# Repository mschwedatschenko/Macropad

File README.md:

# 3x3 Macropad Custom PCB 
This PCB was designed in KiCad and programmed in Arduino IDE using C++. I used OSHPark as my manufacturer of choice, and got some beautiful purple PCBs with ENIG surface finish. The Macropad acts as a HID, with each key representing a number 1-9. These keys can be programmed to be anything the user wants.

## Pictures

Here's the schematic of my design:

Here's the PCB layout of my design:

## Notes
I made the switch footprints far too close to one another, so I had to sand down the switches in order for them to be soldered correctly. This design does not support keycaps. Additionally, future iterations should include the Arduino Micro on the board itself, as it is a pain to have the Arduino Micro hanging off.

I'm currently in the process of making a 60% Keyboard PCB. 

## Purpose
After losing access to my mechanical keyboard I used for a while and just relying on my laptop's built-in keyboard, I had the desire to make my own mechanical keyboard completely from scratch. This macropad serves as a precursor to a 60% keyboard I hope to create during this academic year using a bare ATMega32U4 Microcontroller rather than an Arduino Micro, and to test the waters with the project on a smaller scale. 

It made sense to stick with the Arduino Micro for the microcontroller for this project since I will be strictly using through-hole soldering. With the 60% project, having regular access to WPI's reflow oven will yield hopefully better results using SMT soldering (hand soldering all of the pins on the microcontroller sounds like a nightmare).

I hope to make the switches on the 60% keyboard hot-swappable. I used Cherry MX switches for this macropad and soldered them directly to the PCB.

## BOM
Arduino Micro (alternative knockoff linked here)
https://www.amazon.com/dp/B0B6HYLC44?ref=ppx_yo2ov_dt_b_fed_asin_title 

9x THT Diodes
https://www.digikey.com/en/products/detail/onsemi/1N4148/458603 

9x Cherry MX Switches
https://www.digikey.com/en/products/detail/cherry-americas-llc/MX1A-E1NW/20180

1x 2x12 Pin Header
https://www.mouser.com/ProductDetail/Amphenol-FCI/67996-126HLF?qs=zh4O8xspOuwM2BHmqRMfPg%3D%3D&countryCode=US&currencyCode=USD 

Female to Female Jumper Wires
https://www.amazon.com/California-JOS-Breadboard-Optional-Multicolored/dp/B0BRTKTV64?crid=1LACSR79FHSYC&dib=eyJ2IjoiMSJ9.ibSfPMW-D8UnuoyT0yyf3D_lk7qt6Xtf-hseYz3CHE_PSs4KAuAkM15Fy0qTHeL-0sbmZ6xvudwt1mH7ECdw52J8qVeg-_UcOEXbhjt0zu6y_XCODlAWuh6MgwS7A1VJKjYsNmwjxwCTXuMRC-D0OfljqHtJ6zQDzKQ3gSM8hIwX8KOZwJewJkuHyeDDnSRg3klQF3WwJ22bo-lTGaa8bweF99vKP4XyfbRqS5AhPqo.L_8eHglXmOdtWOBj3pQvrHvJbkccanVmh4Z13YR6j0w&dib_tag=se&keywords=jumper%2Bwires%2Bfemale%2Bto%2Bfemale&qid=1765915770&sprefix=jumper%2Bwires%2Bfemale%2Bto%2Bfemale%2Caps%2C134&sr=8-5&th=1

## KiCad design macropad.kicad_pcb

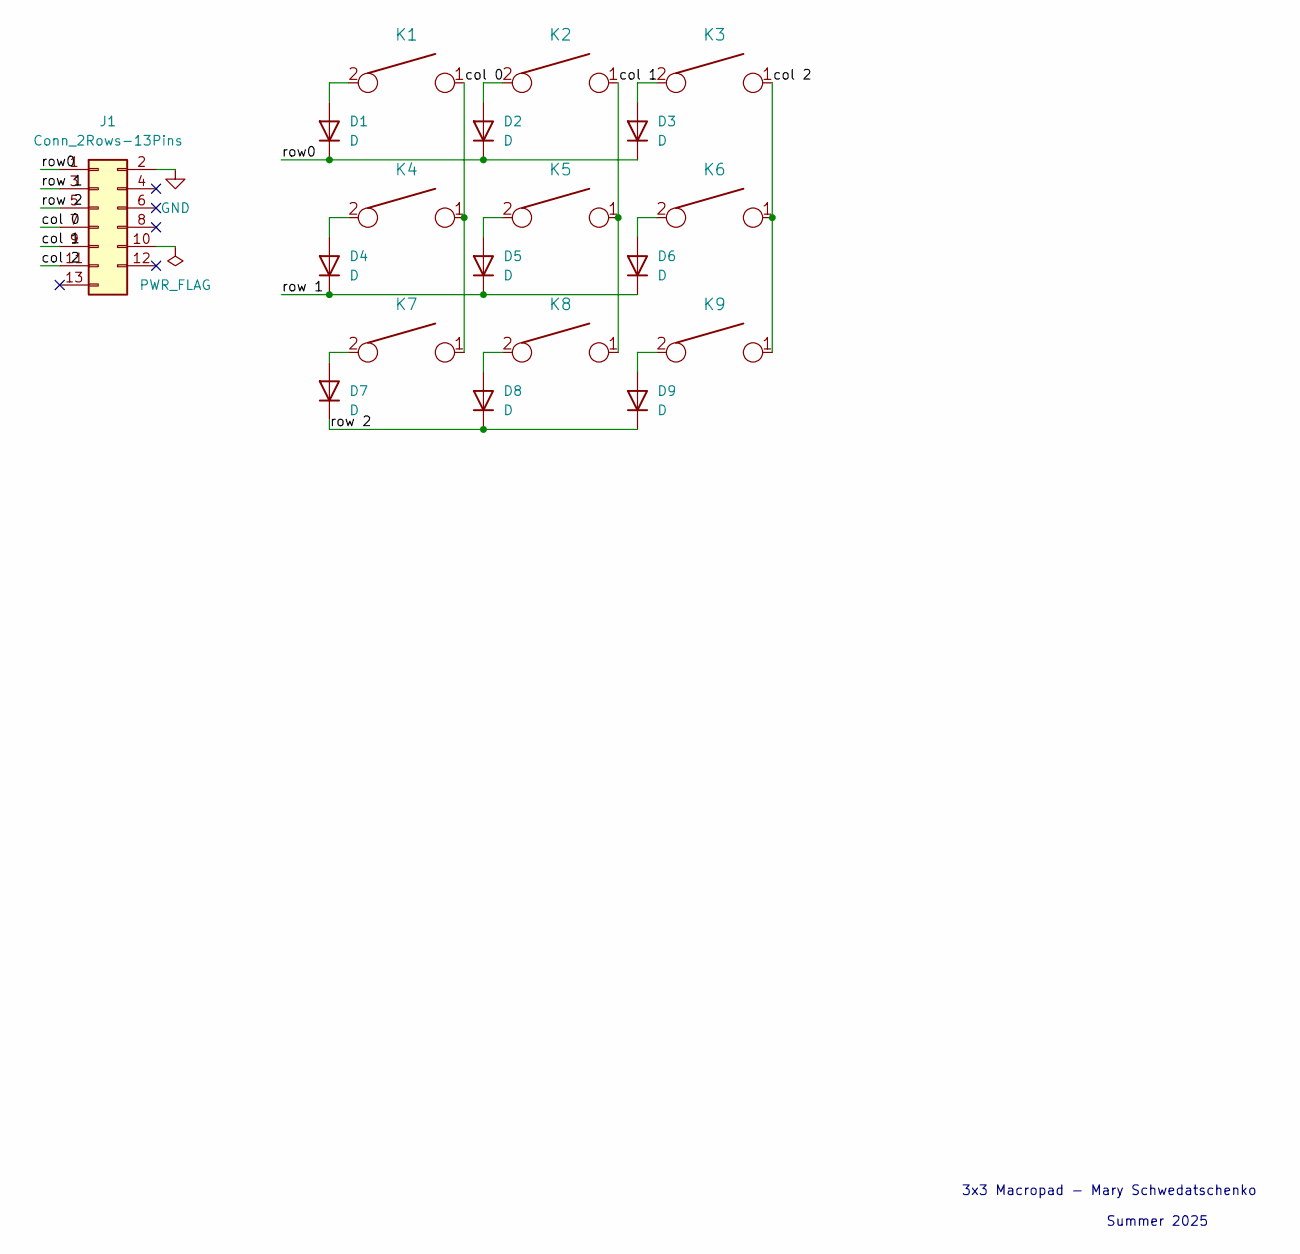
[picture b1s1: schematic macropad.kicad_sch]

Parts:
D1, D2, D3, D4, D5, D6, D7, D8, D9: D; D_DO-35_SOD27_P5.08mm_Vertical_AnodeUp
J1: Conn_2Rows-13Pins; PinHeader_2x13_P2.54mm_Vertical
K1, K2, K3, K4, K5, K6, K7, K8, K9: KEYSW; SW_Cherry_MX_1.00u_PCB

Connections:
/col 0: J1.7, K1.1, K4.1, K7.1
/col 1: J1.9, K2.1, K5.1, K8.1
/col 2: J1.11, K3.1, K6.1, K9.1
/row0: D1.1 (K), D2.1 (K), D3.1 (K), J1.1
/row 1: D4.1 (K), D5.1 (K), D6.1 (K), J1.3
/row 2: D7.1 (K), D8.1 (K), D9.1 (K), J1.5
GND: J1.2
unnamed: D1.2 (A), K1.2
unnamed: D2.2 (A), K2.2
unnamed: D3.2 (A), K3.2
unnamed: D4.2 (A), K4.2
unnamed: D5.2 (A), K5.2
unnamed: D6.2 (A), K6.2
unnamed: D7.2 (A), K7.2
unnamed: D8.2 (A), K8.2
unnamed: D9.2 (A), K9.2

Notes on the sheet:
Summer 2025
3x3 Macropad - Mary Schwedatschenko

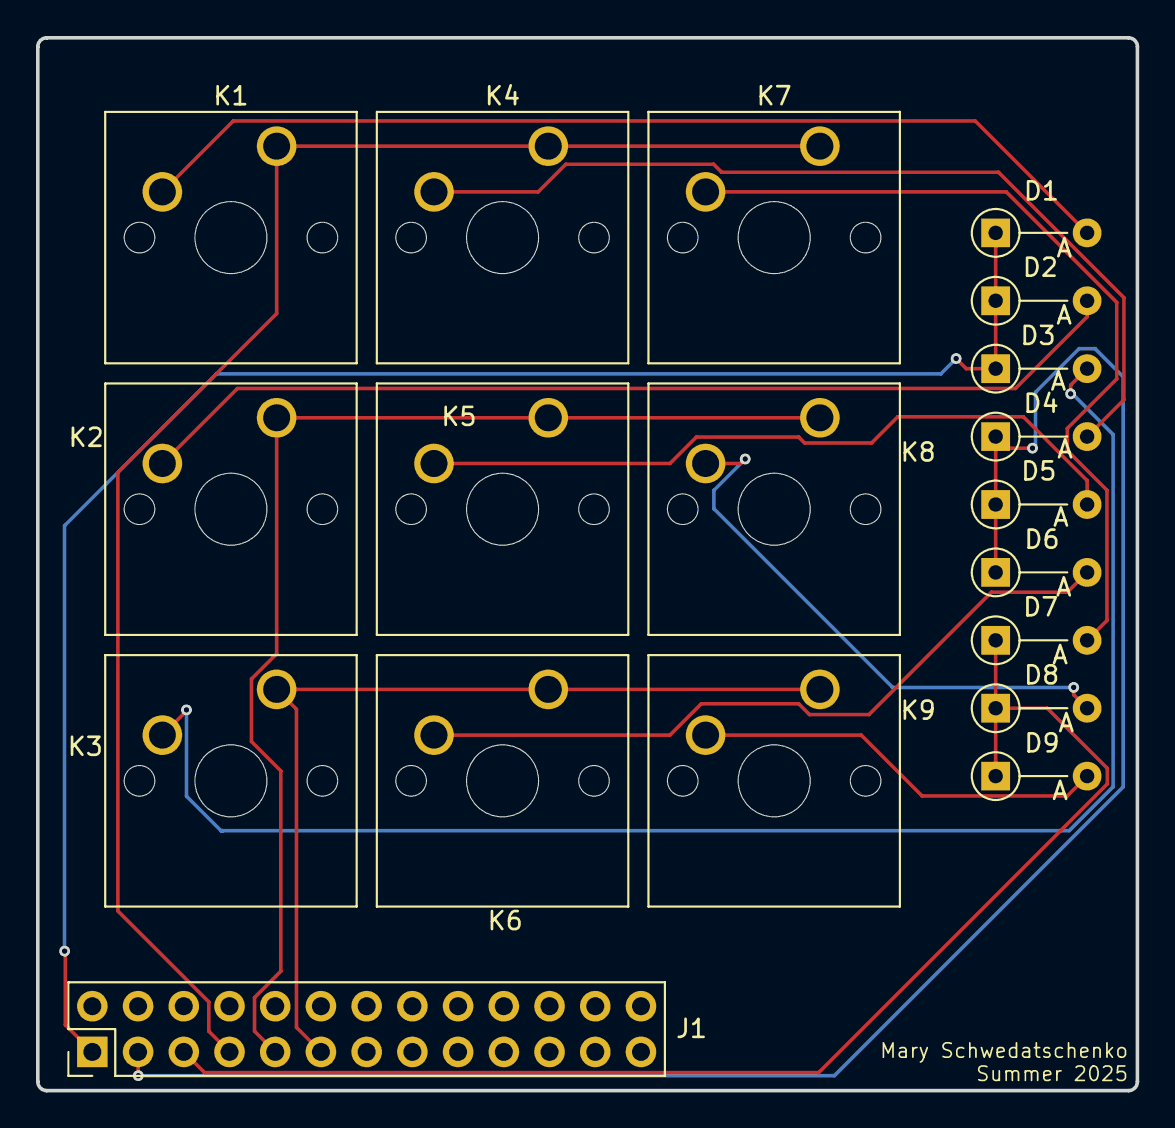
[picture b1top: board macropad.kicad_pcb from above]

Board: 2 copper layers, 61.1 x 58.5 mm, 19 parts (0 on the bottom side), 15 nets.

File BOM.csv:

"Reference","Value","Datasheet","Footprint","Qty","DNP"
"D1,D2,D3,D4,D5,D6,D7,D8,D9","D","~","","9",""
"K1,K2,K3,K4,K5,K6,K7,K8,K9","KEYSW","","","9",""
"U1","Arduino_Micro","https://store.arduino.cc/usa/arduino-micro","Arduino:Arduino_Micro","1",""

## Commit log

2025-06-16 Update README.md
    :P
2025-06-16 initial: switch matrix completed i think
2025-06-16 readme edit
2025-06-16 added board folder
2025-06-17 uh oh this might wreck everything
2025-06-17 deleted vcc
2025-06-17 footprint libs assigned, look for arduino
2025-06-18 added updated bom
2025-07-13 changed symbol to pro micro from arduino micro
2025-07-13 ratsnest
2025-07-13 untracked lck files
2025-07-13 actually untracking .lck hopefully
2025-07-13 untrack .lck plz this time
2025-07-13 no more pro micro footprint, optimized
2025-07-13 recommit
2025-07-15 routed
2025-07-15 forgot to save again -- actually routed
2025-07-15 final tweaks... sent off for manufacturing
2025-07-15 updated bom & readme
2025-07-15 added gerber files & made folders
2025-07-15 condensed
2025-08-02 updated readme, added photos
2025-08-02 pics dint work trying again :(
2025-08-02 3rd image try
2025-08-06 initial switch code for 1 switch -doesn't work
2025-08-08 IT WORKS IT WORKOS YEEESSSS
2025-08-17 code work-macropad done... for now
2025-12-16 updated readme again oops
2026-02-24 Add MIT License
